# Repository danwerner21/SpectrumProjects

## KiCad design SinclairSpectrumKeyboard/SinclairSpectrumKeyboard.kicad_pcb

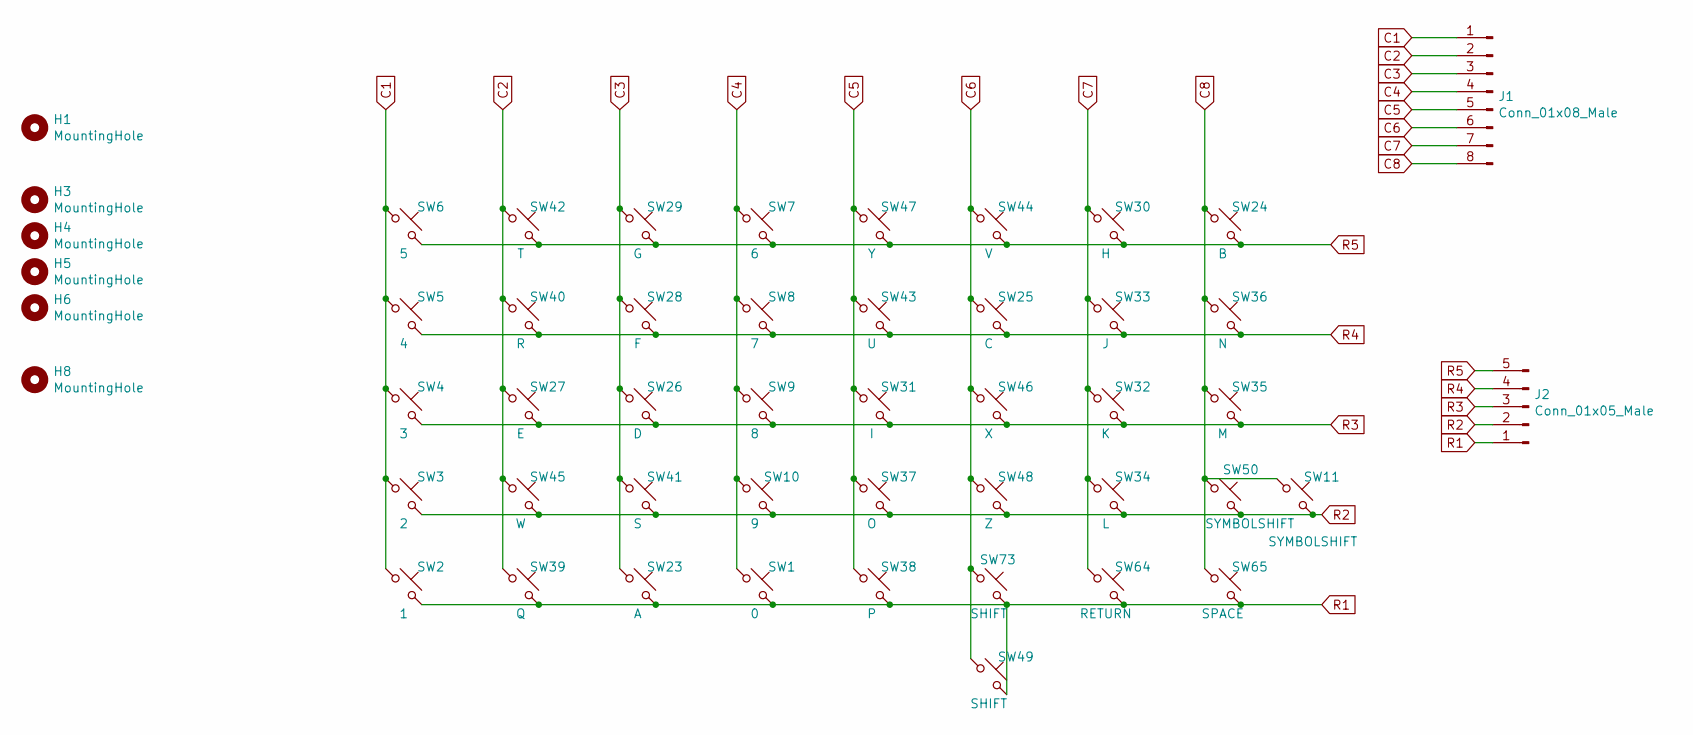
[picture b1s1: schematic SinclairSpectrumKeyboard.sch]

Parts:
H1, H3, H4, H5, H6, H8: MountingHole; MountingHole_3.2mm_M3_Pad
J1: Conn_01x08_Male; PinHeader_1x08_P2.54mm_Vertical
J2: Conn_01x05_Male; PinHeader_1x05_P2.54mm_Vertical
SW1: 0; CHERRY_PCB_100H
SW2: 1; CHERRY_PCB_100H
SW3: 2; CHERRY_PCB_100H
SW4: 3; CHERRY_PCB_100H
SW5: 4; CHERRY_PCB_100H
SW6: 5; CHERRY_PCB_100H
SW7: 6; CHERRY_PCB_100H
SW8: 7; CHERRY_PCB_100H
SW9: 8; CHERRY_PCB_100H
SW10: 9; CHERRY_PCB_100H
SW11: SYMBOLSHIFT; SW_Cherry_MX_1.00u_PCB
SW23: A; CHERRY_PCB_100H
SW24: B; CHERRY_PCB_100H
SW25: C; CHERRY_PCB_100H
SW26: D; CHERRY_PCB_100H
SW27: E; CHERRY_PCB_100H
SW28: F; CHERRY_PCB_100H
SW29: G; CHERRY_PCB_100H
SW30: H; CHERRY_PCB_100H
SW31: I; CHERRY_PCB_100H
SW32: K; CHERRY_PCB_100H
SW33: J; CHERRY_PCB_100H
SW34: L; CHERRY_PCB_100H
SW35: M; CHERRY_PCB_100H
SW36: N; CHERRY_PCB_100H
SW37: O; CHERRY_PCB_100H
SW38: P; CHERRY_PCB_100H
SW39: Q; CHERRY_PCB_100H
SW40: R; CHERRY_PCB_100H
SW41: S; CHERRY_PCB_100H
SW42: T; CHERRY_PCB_100H
SW43: U; CHERRY_PCB_100H
SW44: V; CHERRY_PCB_100H
SW45: W; CHERRY_PCB_100H
SW46: X; CHERRY_PCB_100H
SW47: Y; CHERRY_PCB_100H
SW48: Z; CHERRY_PCB_100H
SW49: SHIFT; CHERRY_PCB_225H
SW50: SYMBOLSHIFT; SW_Cherry_MX_1.75u_PCB
SW64: RETURN; CHERRY_PCB_225H
SW65: SPACE; CHERRY_PCB_625H
SW73: SHIFT; CHERRY_PCB_275H

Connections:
C1: J1.1, SW2.1, SW3.1, SW4.1, SW5.1, SW6.1
C2: J1.2, SW27.1, SW39.1, SW40.1, SW42.1, SW45.1
C3: J1.3, SW23.1, SW26.1, SW28.1, SW29.1, SW41.1
C4: J1.4, SW1.1, SW7.1, SW8.1, SW9.1, SW10.1
C5: J1.5, SW31.1, SW37.1, SW38.1, SW43.1, SW47.1
C6: J1.6, SW25.1, SW44.1, SW46.1, SW48.1, SW49.1, SW73.1
C7: J1.7, SW30.1, SW32.1, SW33.1, SW34.1, SW64.1
C8: J1.8, SW11.1, SW24.1, SW35.1, SW36.1, SW50.1, SW65.1
R1: J2.1, SW1.2, SW2.2, SW23.2, SW38.2, SW39.2, SW49.2, SW64.2, SW65.2, SW73.2
R2: J2.2, SW3.2, SW10.2, SW11.2, SW34.2, SW37.2, SW41.2, SW45.2, SW48.2, SW50.2
R3: J2.3, SW4.2, SW9.2, SW26.2, SW27.2, SW31.2, SW32.2, SW35.2, SW46.2
R4: J2.4, SW5.2, SW8.2, SW25.2, SW28.2, SW33.2, SW36.2, SW40.2, SW43.2
R5: J2.5, SW6.2, SW7.2, SW24.2, SW29.2, SW30.2, SW42.2, SW44.2, SW47.2

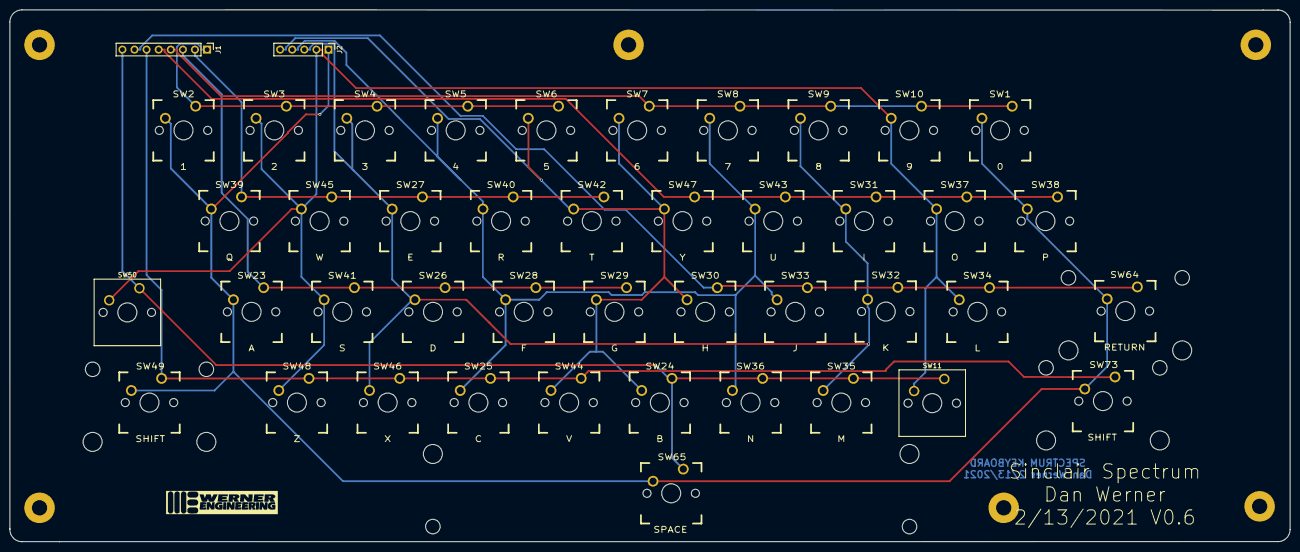
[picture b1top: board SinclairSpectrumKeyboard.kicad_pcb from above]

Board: 2 copper layers, 268.8 x 111.7 mm, 50 parts (0 on the bottom side), 13 nets.

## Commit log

2022-07-05 initial
